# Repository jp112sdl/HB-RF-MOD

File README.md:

# HB-RF-MOD
Alternative Platine zum RPI-RF-MOD, um das Funkmodul "richtig herum" auf den Raspberry Pi aufsetzen zu können.

**19.11.2020 - die Platinen sind da** <br>

<br/><br/>
**20.11.2020 - erster Aufbau und voller Erfolg!** :tada: <br/>
<br/>

<br/>

<br/>

**21.11.2020 - Inbetriebnahme**<br/>

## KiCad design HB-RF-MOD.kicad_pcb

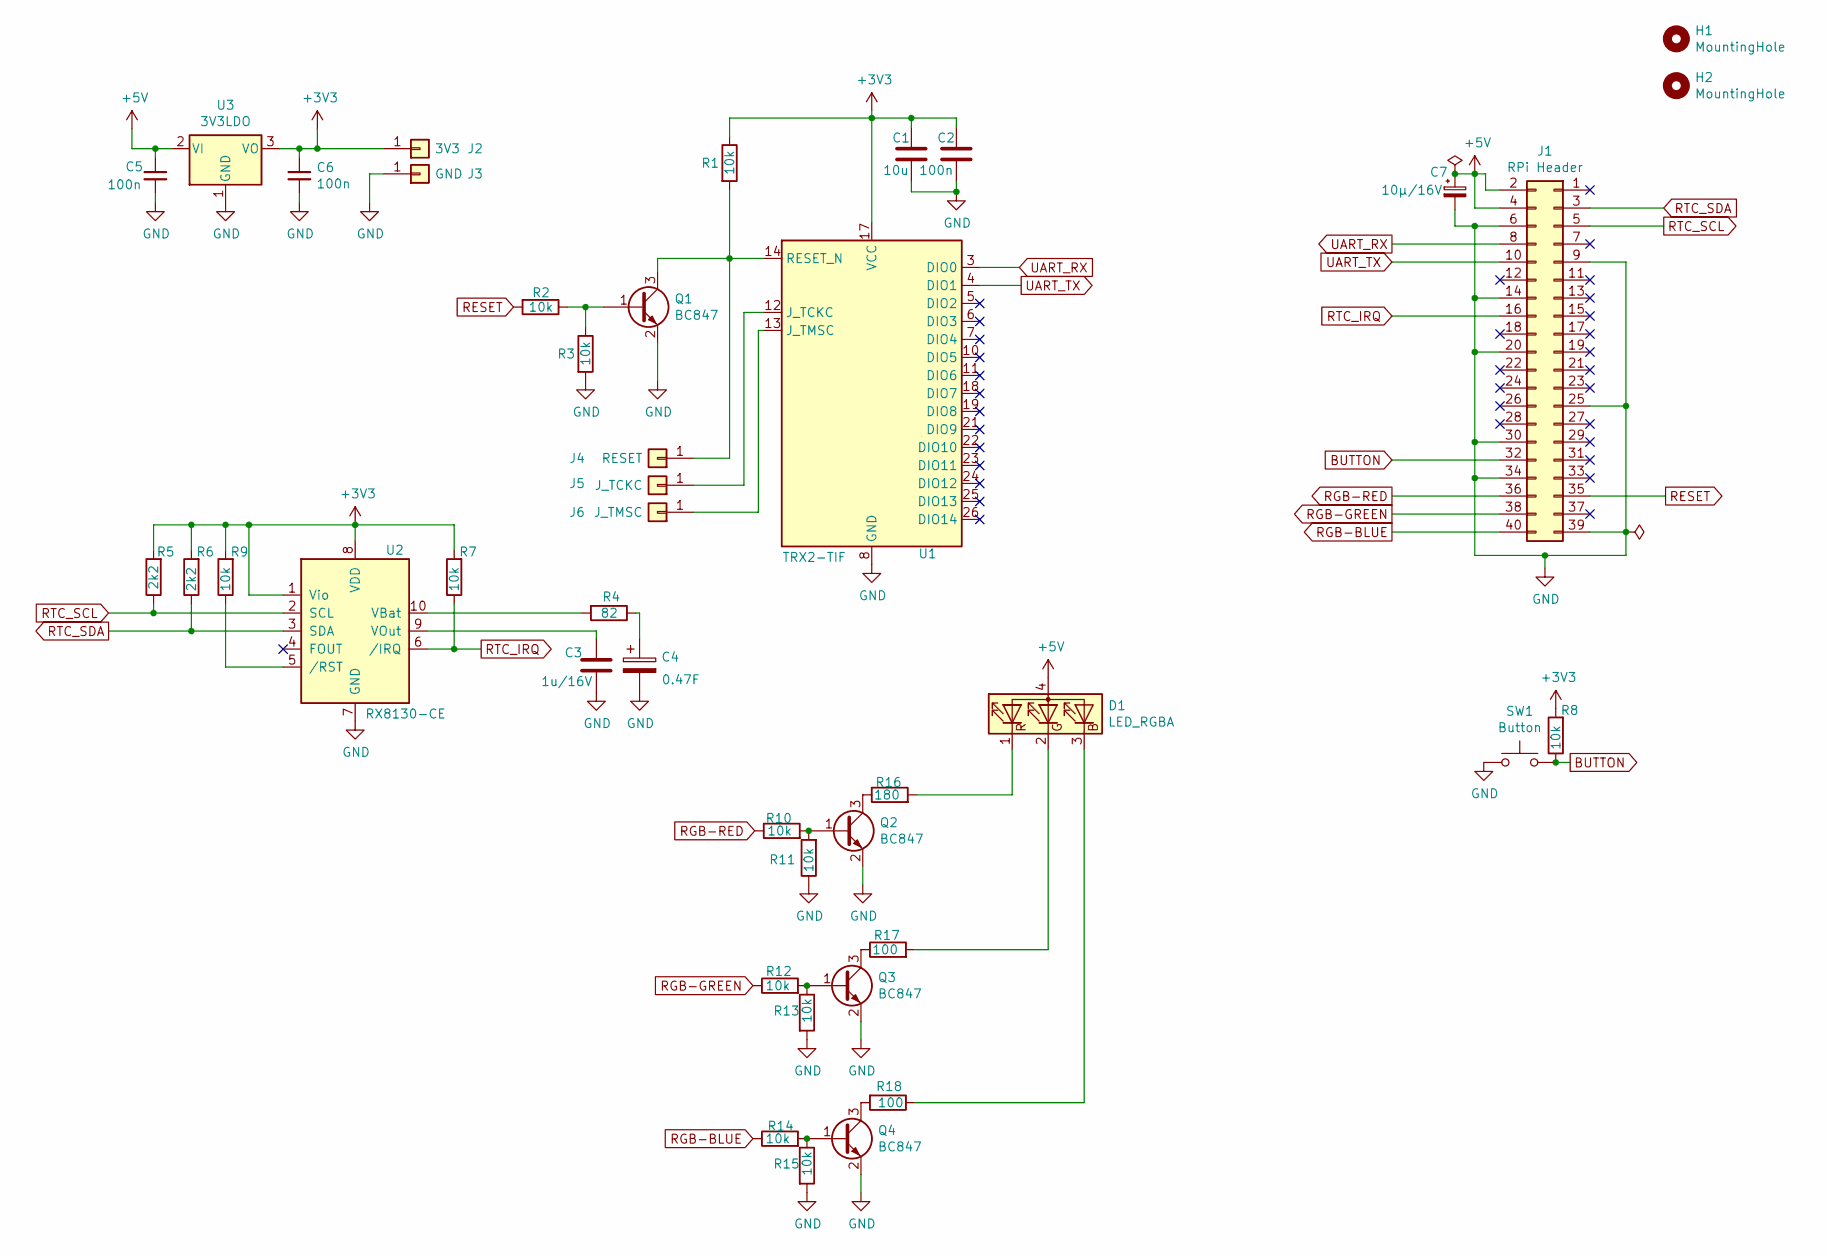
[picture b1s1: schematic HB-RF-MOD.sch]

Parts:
C1: 10u; C_0805_2012Metric_Pad1.15x1.40mm_HandSolder
C2, C5, C6: 100n; C_0805_2012Metric_Pad1.15x1.40mm_HandSolder
C3: 1u/16V; C_0805_2012Metric_Pad1.15x1.40mm_HandSolder
C4: 0.47F; CP_Radial_D20.0mm_P5.00mm
C7: 10µ/16V; CP_Elec_6.3x5.9
D1: LED_RGBA; LED_D5.0mm-4_RGB_Wide_Pins
H1, H2: MountingHole; MountingHole_2.7mm_M2.5_DIN965
J1: RPi Header; PinSocket_2x20_P2.54mm_Vertical
J2: 3V3; TestPoint_Pad_D1.5mm
J3: GND; TestPoint_Pad_D1.5mm
J4: RESET; TestPoint_Pad_D1.5mm
J5: J_TCKC; TestPoint_Pad_D1.5mm
J6: J_TMSC; TestPoint_Pad_D1.5mm
Q1, Q2, Q3, Q4: BC847; SOT-23
R1, R2, R3, R7, R8, R9, R10, R11, R12, R13, R14, R15: 10k; R_0805_2012Metric_Pad1.15x1.40mm_HandSolder
R4: 82; R_0805_2012Metric_Pad1.15x1.40mm_HandSolder
R5, R6: 2k2; R_0805_2012Metric_Pad1.15x1.40mm_HandSolder
R16: 180; R_0805_2012Metric_Pad1.15x1.40mm_HandSolder
R17, R18: 100; R_0805_2012Metric_Pad1.15x1.40mm_HandSolder
SW1: Button; SW_SPST_PTS810
U1: TRX2-TIF
U2: RX8130-CE; SMD-3225-10Pin_3.2x2.5mm_HandSoldering
U3: 3V3LDO; SOT-89-3

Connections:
+3V3: C1.1, C2.1, C6.1, J2.1, R1.1, R5.2, R6.2, R7.2, R8.2, R9.2, U1.17 (VCC), U2.1 (Vio), U2.8 (VDD), U3.3 (VO)
+5V: C5.1, C7.1, D1.4 (A), J1.2, J1.4, U3.2 (VI)
BUTTON: J1.32, R8.1, SW1.2
GND: C1.2, C2.2, C3.2, C4.2, C5.2, C6.2, C7.2, J1.6, J1.9, J1.14, J1.20, J1.25, J1.30, J1.34, J1.39, J3.1, Q1.2 (E), Q2.2 (E), Q3.2 (E), Q4.2 (E), R3.2, R11.1, R13.2, R15.2, SW1.1, U1.8 (GND), U1.9 (GND), U1.15 (GND), U1.16 (GND), U1.20 (GND), U2.7 (GND), U3.1 (GND)
unnamed: C3.1, U2.9 (VOut)
unnamed: C4.1, R4.1
unnamed: D1.1 (RK), R16.2
unnamed: D1.2 (GK), R17.2
unnamed: D1.3 (BK), R18.1
unnamed: J4.1, Q1.3 (C), R1.2, U1.14 (RESET_N)
unnamed: J5.1, U1.12 (J_TCKC)
unnamed: J6.1, U1.13 (J_TMSC)
unnamed: Q1.1 (B), R2.1, R3.1
unnamed: Q2.1 (B), R10.2, R11.2
unnamed: Q2.3 (C), R16.1
unnamed: Q3.1 (B), R12.2, R13.1
unnamed: Q3.3 (C), R17.1
unnamed: Q4.1 (B), R14.2, R15.1
unnamed: Q4.3 (C), R18.2
unnamed: R4.2, U2.10 (VBat)
unnamed: R9.1, U2.5 (/RST)
RESET: J1.35, R2.2
RGB-BLUE: J1.40, R14.1
RGB-GREEN: J1.38, R12.1
RGB-RED: J1.36, R10.1
RTC_IRQ: J1.16, R7.1, U2.6 (/IRQ)
RTC_SCL: J1.5, R5.1, U2.2 (SCL)
RTC_SDA: J1.3, R6.1, U2.3 (SDA)
UART_RX: J1.8, U1.3 (DIO0)
UART_TX: J1.10, U1.4 (DIO1)

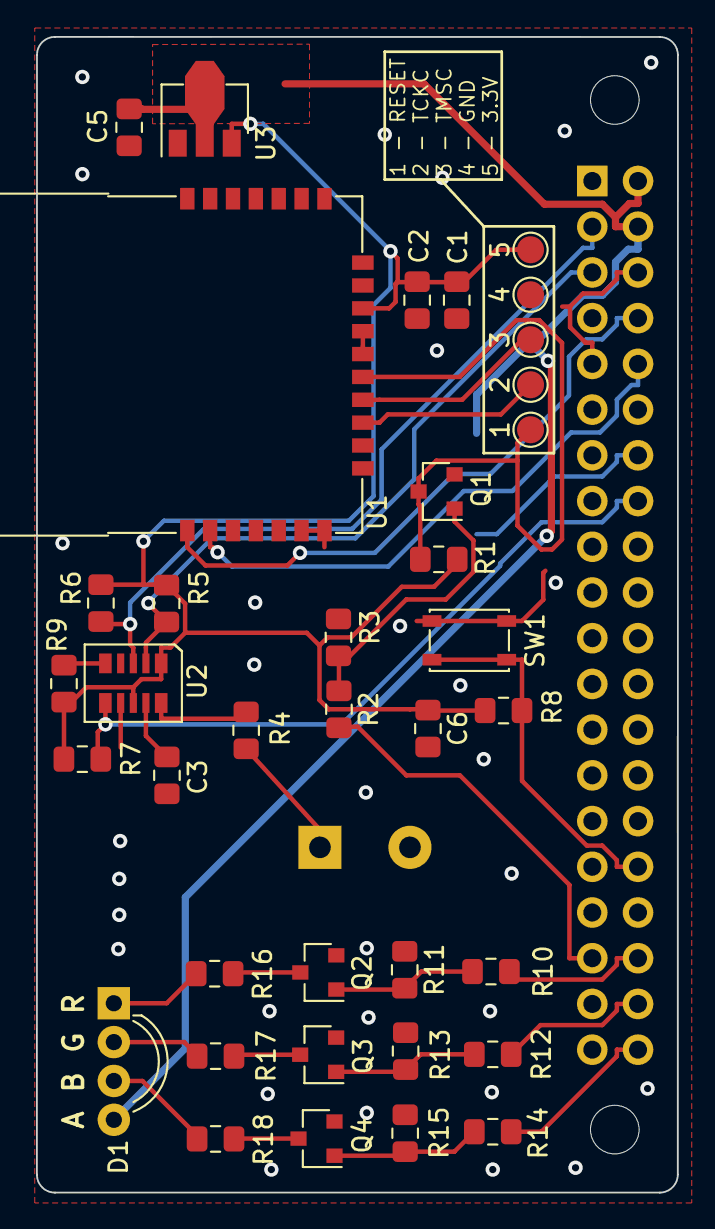
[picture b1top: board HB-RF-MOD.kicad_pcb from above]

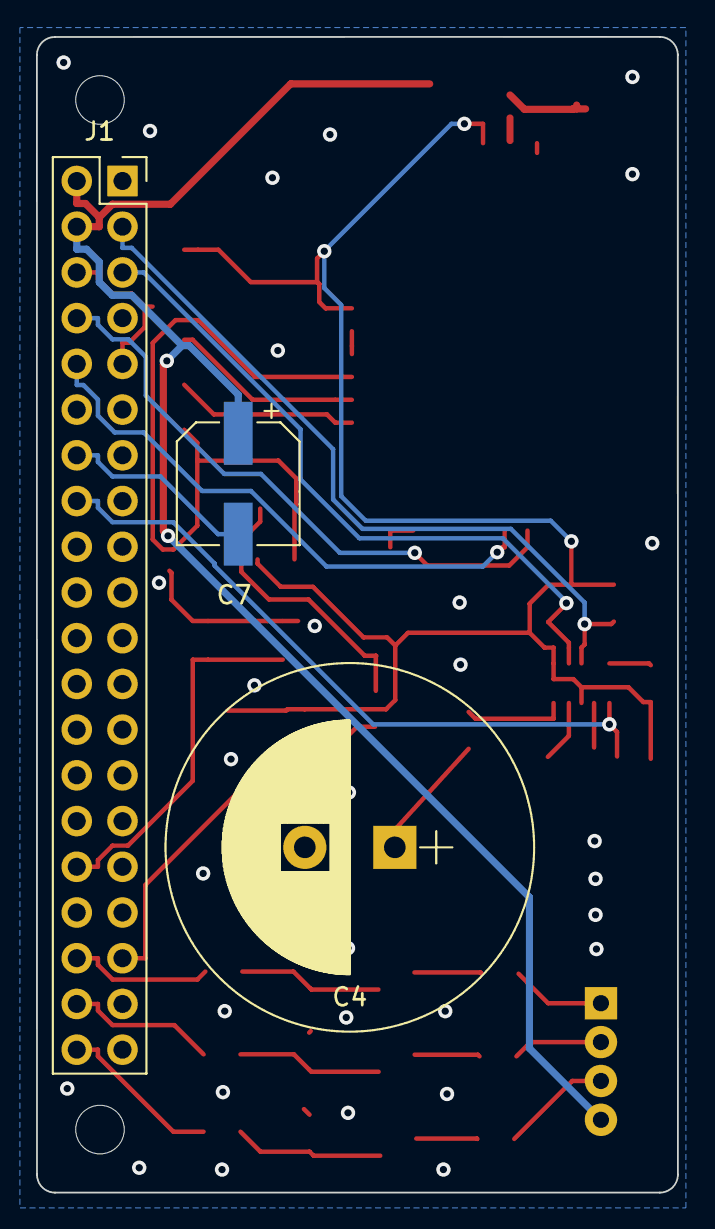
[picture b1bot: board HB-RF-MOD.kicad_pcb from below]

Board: 2 copper layers, 35.6 x 64.2 mm, 42 parts (3 on the bottom side), 30 nets.

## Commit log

2020-11-06 add 3D modell of TRX2-TIF
2020-11-09 resize image
2020-11-09 update pcb
2020-11-20 add images
2020-11-21 add image
